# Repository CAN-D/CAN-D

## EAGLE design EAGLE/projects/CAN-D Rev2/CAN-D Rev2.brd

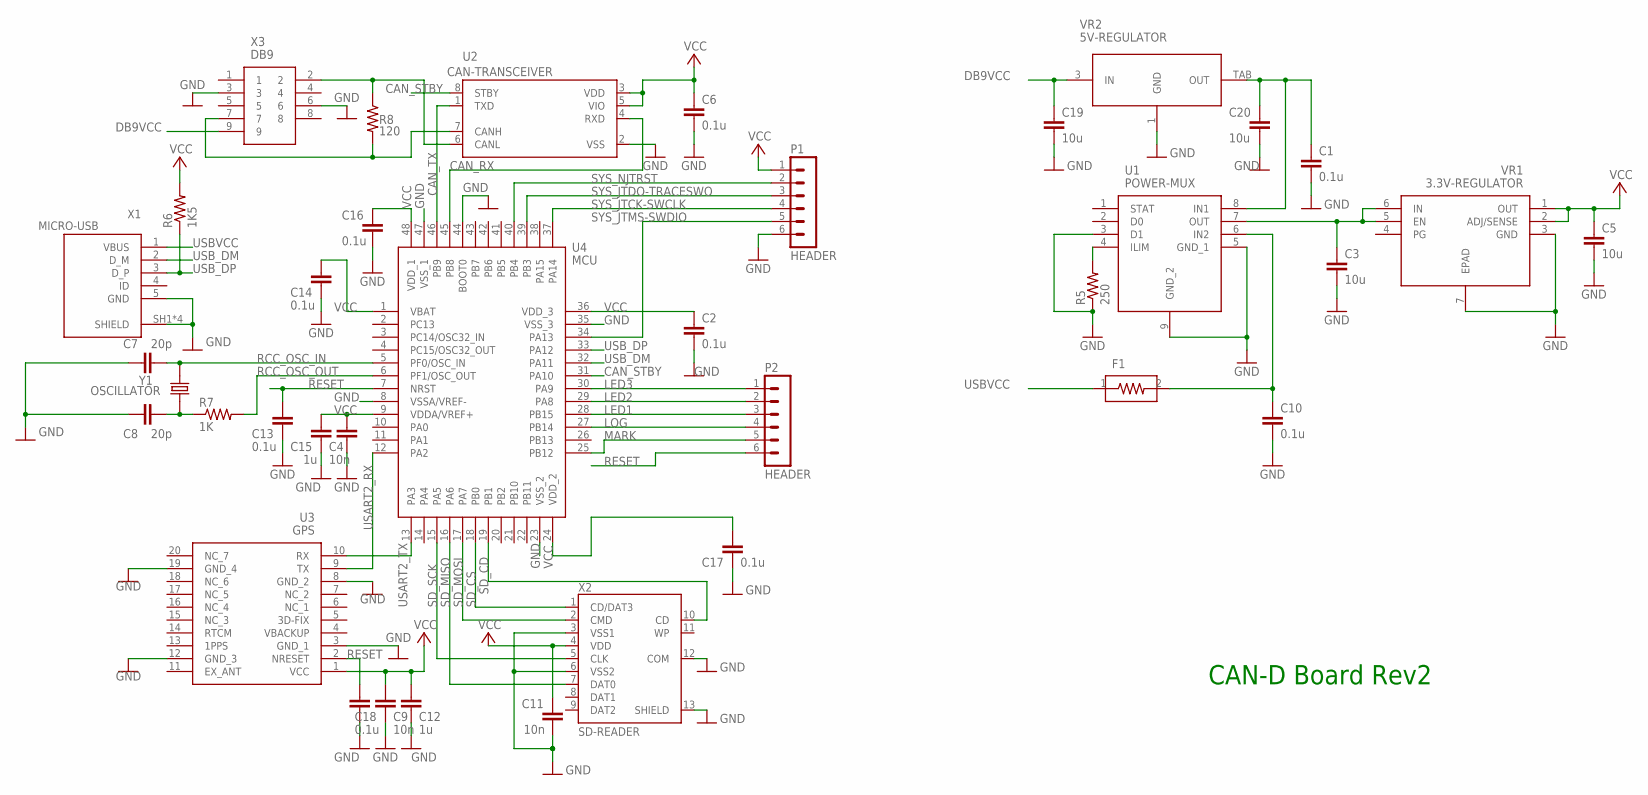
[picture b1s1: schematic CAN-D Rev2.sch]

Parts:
C1, C2, C6, C10, C13, C14, C16, C17, C18: 0.1u; C0603
C3, C5, C19, C20: 10u; C0603
C4, C9, C11: 10n; C0603
C7, C8: 20p; C0603
C12, C15: 1u; C0603
F1: FUSE; 0ZCJ0025FF2E
P1, P2: HEADER; TSM-106-02-L-SV-P-TR
R5: 250; R0603
R6: 1K5; R0603
R7: 1K; R0603
R8: 120; R0603
U1: POWER-MUX; TPS2115ADRBR
U2: CAN-TRANSCEIVER; MCP2562-E/SN
U3: GPS; FGPMMOPA6H
U4: MCU; STM32F302CCT6
VR1: 3.3V-REGULATOR; LD39200PU33R
VR2: 5V-REGULATOR; LD1086D2T50TR
X1: MICRO-USB; DX4R005HJ5R2000
X2: SD-READER; DM1AA-SF-PEJ(21)
X3: DB9; 1-1740195-2
Y1: OSCILLATOR; ABLS-8.000MHZ-B2-T

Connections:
CAN_RX: U2.4 (RXD), U4.45 (PB8)
CAN_STBY: U2.8 (STBY), U4.31 (PA10)
CAN_TX: U2.1 (TXD), U4.46 (PB9)
DB9VCC: C19.1, VR2.3 (IN), X3.9
GND: C1.2, C2.2, C3.2, C4.2, C5.2, C6.2, C7.2, C8.2, C9.2, C10.2, C11.2, C12.2, C13.2, C14.2, C15.2, C16.2, C17.2, C18.2, C19.2, C20.2, P1.6, R5.1, U1.3 (D1), U1.5 (GND_1), U1.9 (GND_2), U2.2 (VSS), U3.3 (GND_1), U3.8 (GND_2), U3.12 (GND_3), U3.19 (GND_4), U4.8 (VSSA/VREF-), U4.23 (VSS_2), U4.35 (VSS_3), U4.44 (BOOT0), U4.47 (VSS_1), VR1.3 (GND), VR1.7 (EPAD), VR2.1 (GND), X1.5 (GND), X1.SH1 (SHIELD), X1.SH2 (SHIELD), X1.SH3 (SHIELD), X1.SH4 (SHIELD), X2.3 (VSS1), X2.6 (VSS2), X2.12 (COM), X2.13 (SHIELD), X3.3, X3.6
LED1: P2.3, U4.28 (PB15)
LED2: P2.2, U4.29 (PA8)
LED3: P2.1, U4.30 (PA9)
LOG: P2.4, U4.27 (PB14)
MARK: P2.5, U4.25 (PB12)
unnamed: C3.1, U1.7 (OUT), VR1.5 (EN), VR1.6 (IN)
unnamed: R8.2, U2.7 (CANH), X3.7
unnamed: C1.1, C20.1, U1.8 (IN1), VR2.TAB (OUT)
unnamed: R8.1, U2.6 (CANL), X3.2
unnamed: R5.2, U1.4 (ILIM)
unnamed: C10.1, F1.2, U1.6 (IN2)
unnamed: C8.1, R7.1, Y1.1
RCC_OSC_IN: C7.1, U4.5 (PF0/OSC_IN), Y1.2
RCC_OSC_OUT: R7.2, U4.6 (PF1/OSC_OUT)
RESET: C13.1, C18.1, P2.6, U3.2 (NRESET), U4.7 (NRST)
SD_CD: U4.19 (PB1), X2.10 (CD)
SD_CS: U4.18 (PB0), X2.1 (CD/DAT3)
SD_MISO: U4.16 (PA6), X2.7 (DAT0)
SD_MOSI: U4.17 (PA7), X2.2 (CMD)
SD_SCK: U4.15 (PA5), X2.5 (CLK)
SYS_JTCK-SWCLK: P1.4, U4.37 (PA14)
SYS_JTDO-TRACESWO: P1.3, U4.39 (PB3)
SYS_JTMS-SWDIO: P1.5, U4.34 (PA13)
SYS_NJTRST: P1.2, U4.40 (PB4)
USART2_RX: U3.9 (TX), U4.12 (PA2)
USART2_TX: U3.10 (RX), U4.13 (PA3)
USBVCC: F1.1, X1.1 (VBUS)
USB_DM: U4.32 (PA11), X1.2 (D_M)
USB_DP: R6.1, U4.33 (PA12), X1.3 (D_P)
VCC: C2.1, C4.1, C5.1, C6.1, C9.1, C11.1, C12.1, C14.1, C15.1, C16.1, C17.1, P1.1, R6.2, U2.3 (VDD), U2.5 (VIO), U3.1 (VCC), U4.1 (VBAT), U4.9 (VDDA/VREF+), U4.24 (VDD_2), U4.36 (VDD_3), U4.48 (VDD_1), VR1.1 (OUT), VR1.2 (ADJ/SENSE), X2.4 (VDD)

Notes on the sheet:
CAN-D Board Rev2

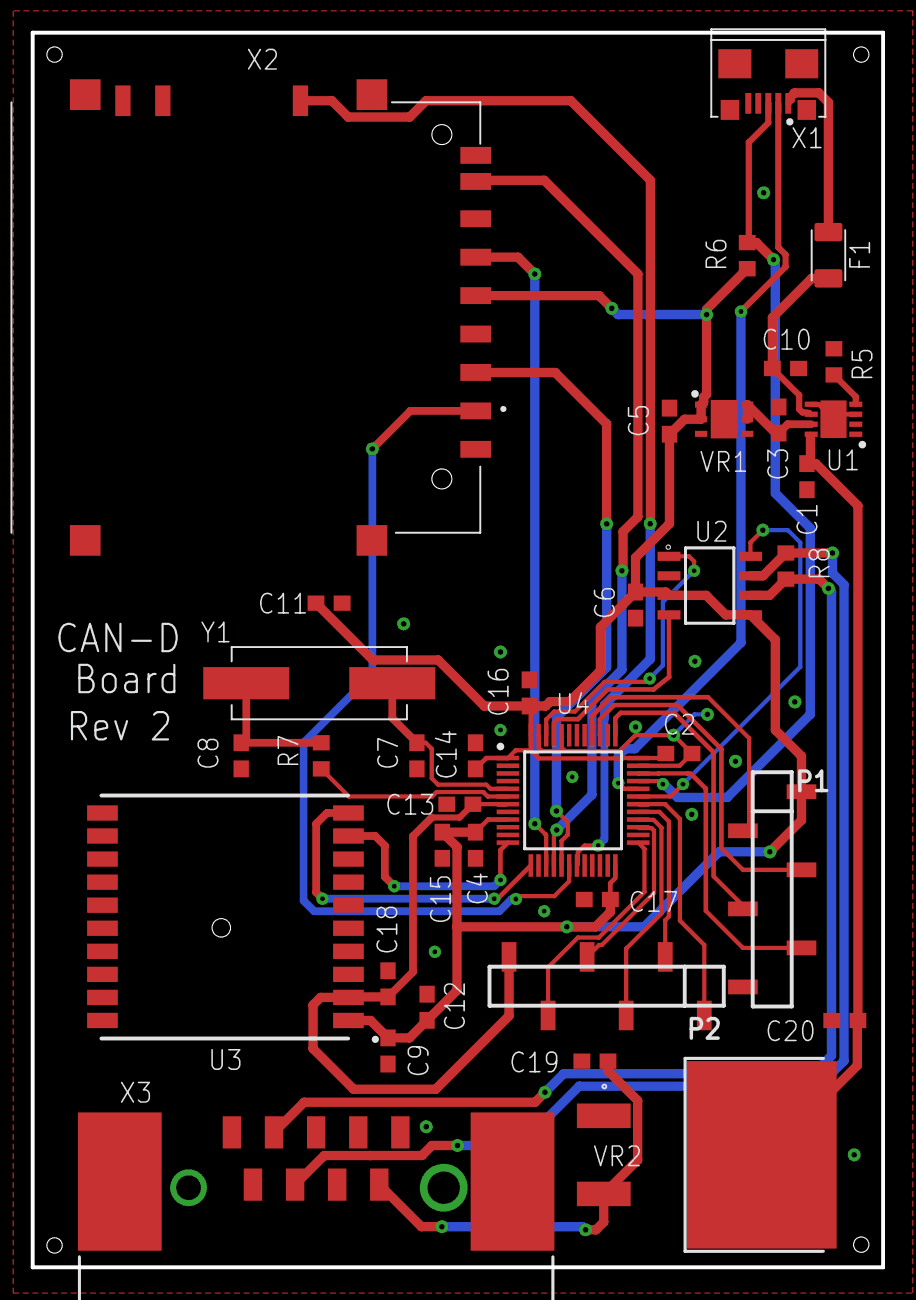
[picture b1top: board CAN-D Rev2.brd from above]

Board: 2 copper layers, 55.3 x 80.3 mm, 37 parts (0 on the bottom side), 35 nets.

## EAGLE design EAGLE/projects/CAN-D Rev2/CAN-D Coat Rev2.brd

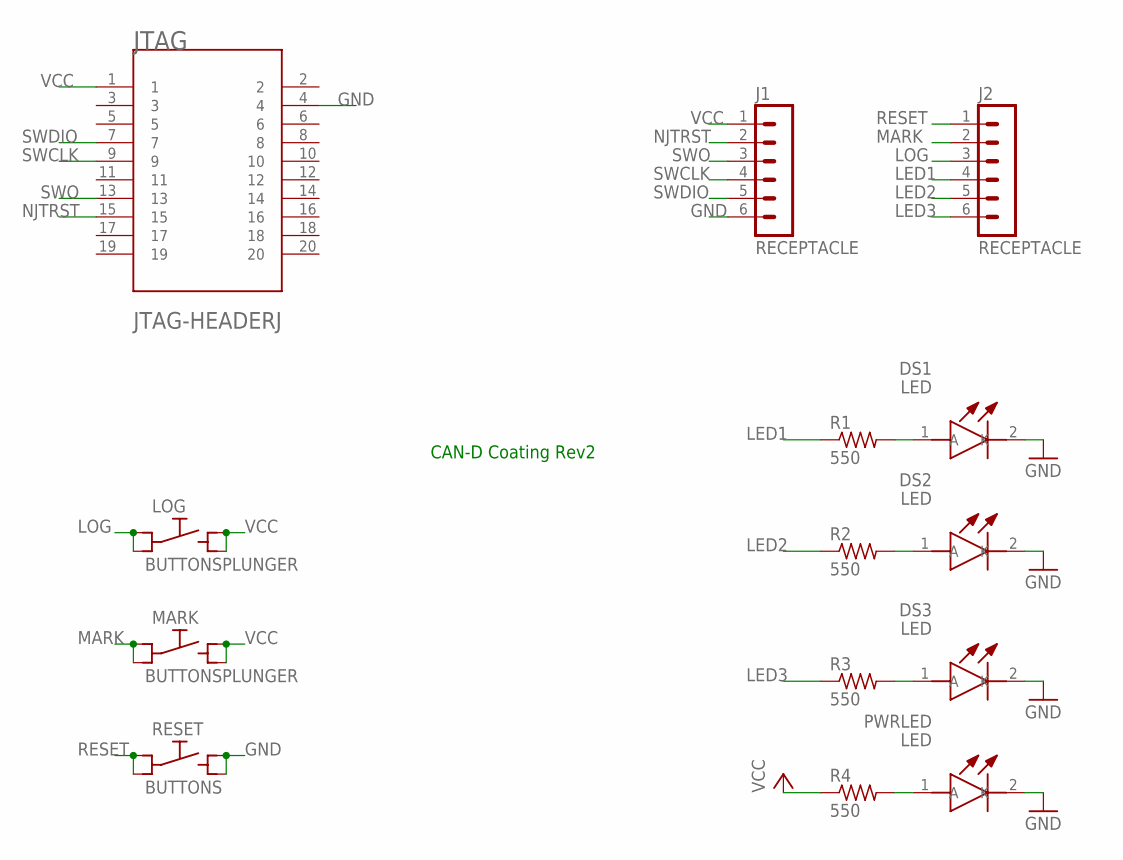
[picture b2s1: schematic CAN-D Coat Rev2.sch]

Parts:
DS1, DS2, DS3: LED; L130-6580001400001
J1, J2: RECEPTACLE; SSM-106-L-SV-K-TR
JTAG: JTAG-HEADERJ; TSM-110-02-S-DV-P-TR
LOG: BUTTONSPLUNGER; TL3301SPF260QG
MARK: BUTTONSPLUNGER; TL3301SPF260QG
PWRLED: LED; L130-6580001400001
R1, R2, R3, R4: 550; R0603
RESET: BUTTONS; 1301.9314

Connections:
GND: DS1.2 (K), DS2.2 (K), DS3.2 (K), J1.6, JTAG.4, PWRLED.2 (K), RESET.NO1 (NO), RESET.NO2 (NO)
LED1: J2.4, R1.1
LED2: J2.5, R2.1
LED3: J2.6, R3.1
LOG: J2.3, LOG.C1 (C), LOG.C2 (C)
MARK: J2.2, MARK.C1 (C), MARK.C2 (C)
unnamed: DS1.1 (A), R1.2
unnamed: DS2.1 (A), R2.2
unnamed: DS3.1 (A), R3.2
unnamed: PWRLED.1 (A), R4.2
NJTRST: J1.2, JTAG.15
RESET: J2.1, RESET.C1 (C), RESET.C2 (C)
SWCLK: J1.4, JTAG.9
SWDIO: J1.5, JTAG.7
SWO: J1.3, JTAG.13
VCC: J1.1, JTAG.1, LOG.NO1 (NO), LOG.NO2 (NO), MARK.NO1 (NO), MARK.NO2 (NO), R4.1

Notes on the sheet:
CAN-D Coating Rev2

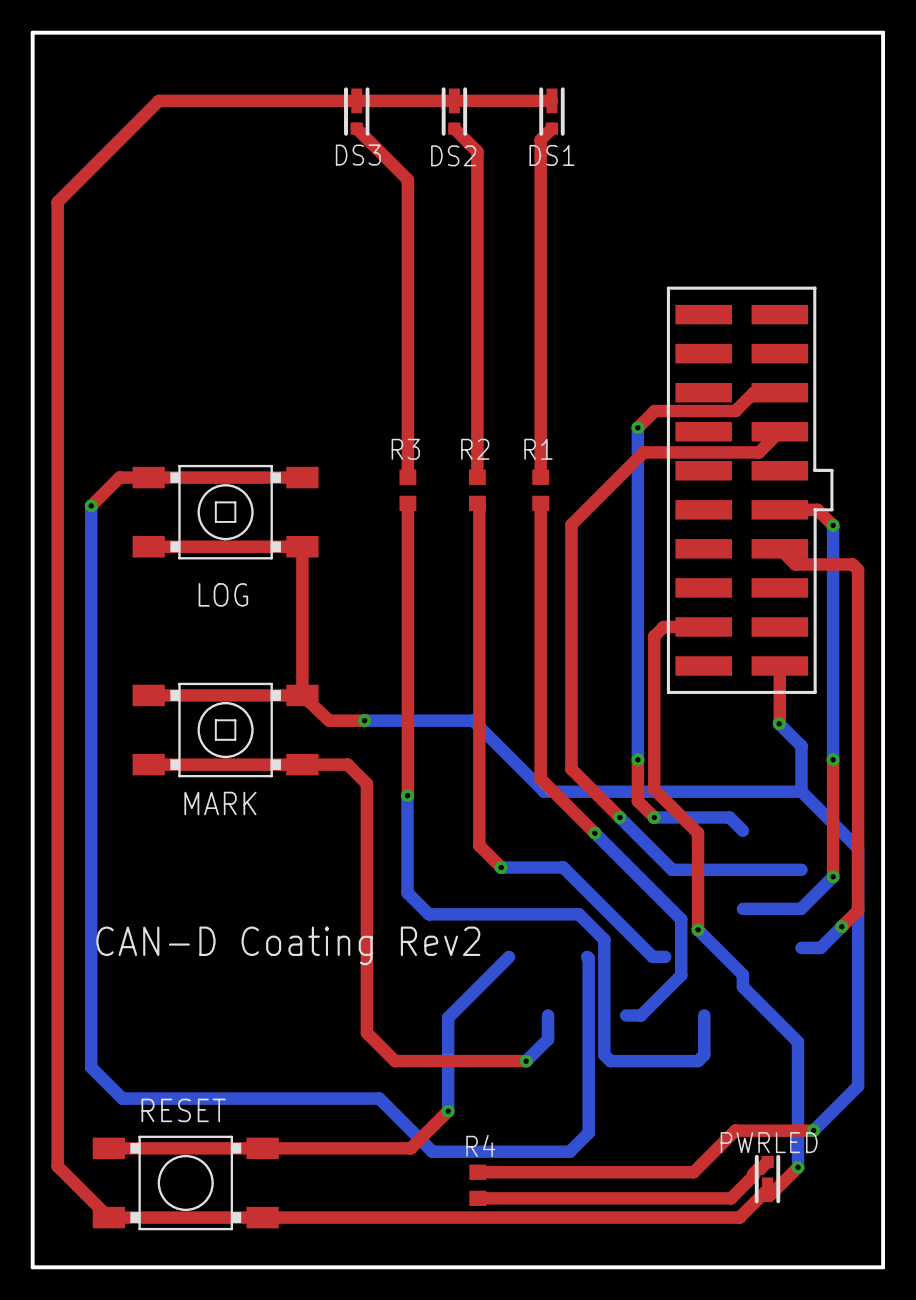
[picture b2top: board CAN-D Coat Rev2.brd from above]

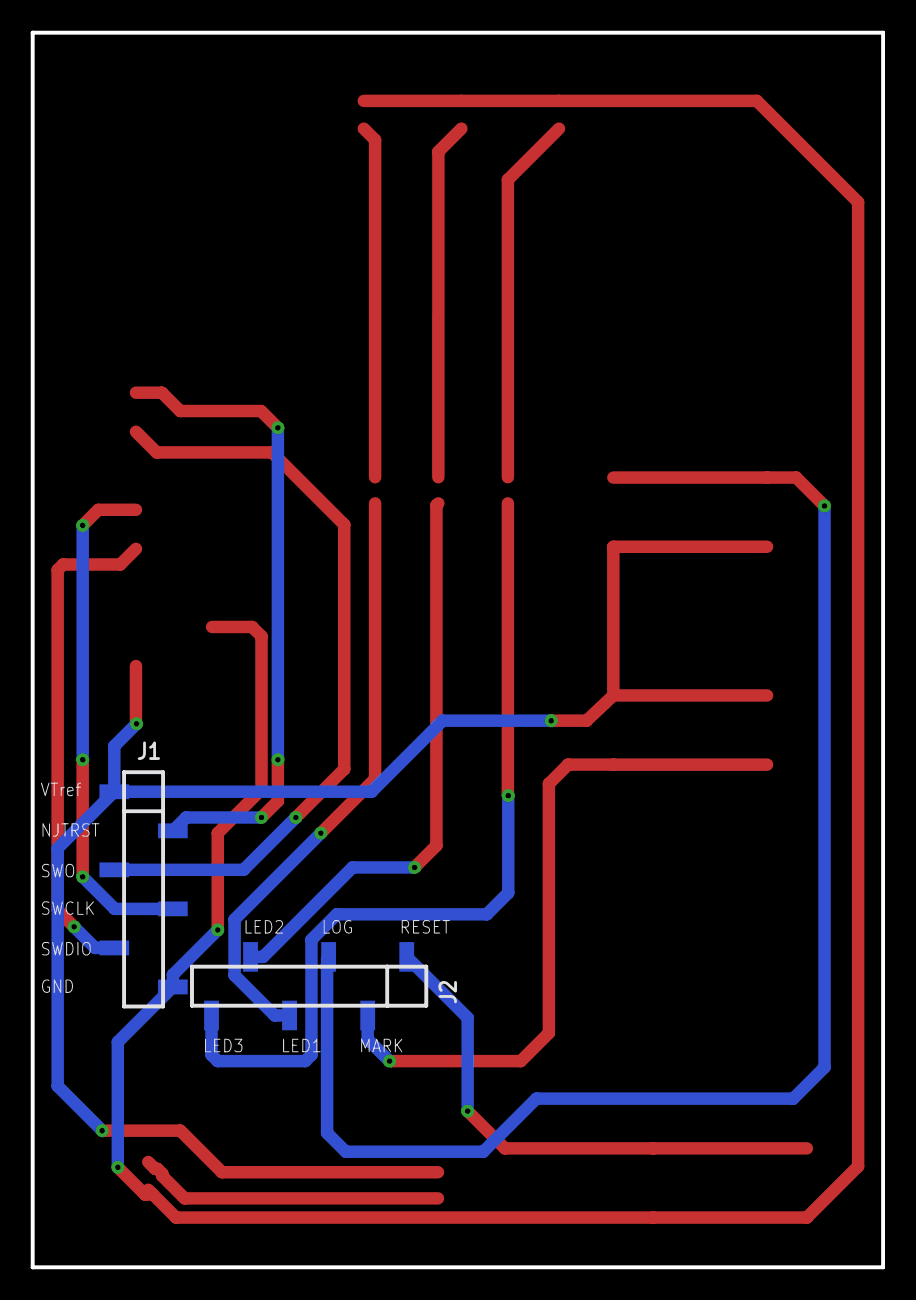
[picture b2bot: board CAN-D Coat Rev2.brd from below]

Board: 2 copper layers, 55.3 x 80.3 mm, 14 parts (2 on the bottom side), 16 nets.

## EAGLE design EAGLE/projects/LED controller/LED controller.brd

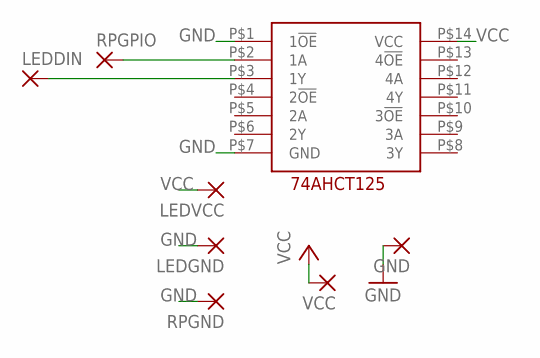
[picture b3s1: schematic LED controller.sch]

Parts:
GND: 1,6/0,9
LEDDIN: 1,6/0,9
LEDGND: 1,6/0,9
LEDVCC: 1,6/0,9
RPGND: 1,6/0,9
RPGPIO: 1,6/0,9
U$1: 74AHCT125N14; N14
VCC: 1,6/0,9

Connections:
GND: GND.1, LEDGND.1, RPGND.1, U$1.P$1 (1!OE!), U$1.P$7 (GND)
unnamed: RPGPIO.1, U$1.P$2 (1A)
unnamed: LEDDIN.1, U$1.P$3 (1Y)
VCC: LEDVCC.1, U$1.P$14 (VCC), VCC.1

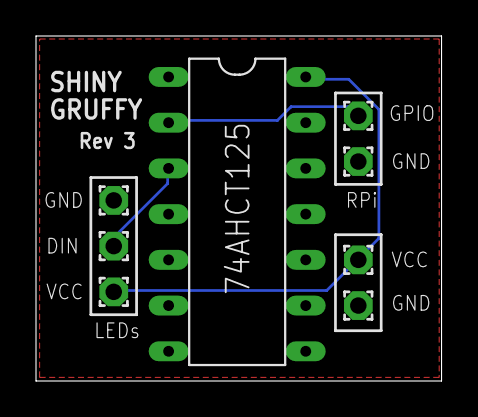
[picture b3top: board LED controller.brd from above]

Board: 2 copper layers, 22.5 x 19.2 mm, 8 parts (0 on the bottom side), 4 nets.

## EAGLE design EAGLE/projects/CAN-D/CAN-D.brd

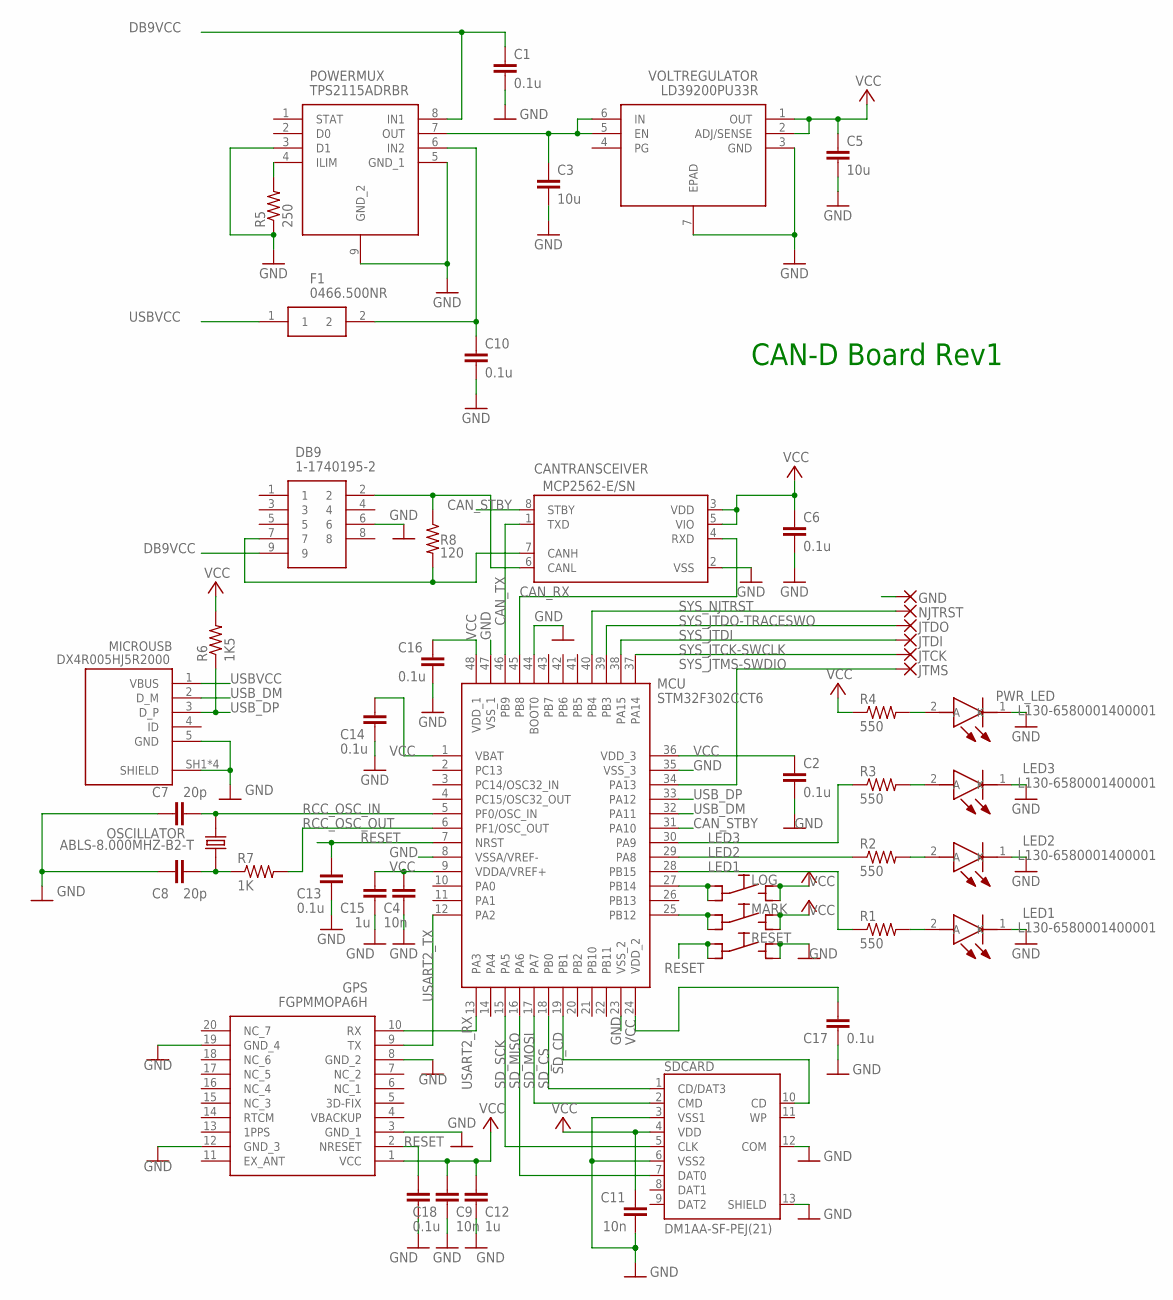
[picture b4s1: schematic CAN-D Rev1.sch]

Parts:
C1, C2, C6, C10, C13, C14, C16, C17, C18: 0.1u; C0603
C3, C5: 10u; C0603
C4, C9, C11: 10n; C0603
C7, C8: 20p; C0603
C12, C15: 1u; C0603
CANTRANSCEIVER: MCP2562-E/SN; SOIC127P600X175-8N
DB9: 1-1740195-2
F1: 0466.500NR; FUSC3215X58N
GND: 2,54/1,1
GPS: FGPMMOPA6H
JTCK: 2,54/1,1
JTDI: 2,54/1,1
JTDO: 2,54/1,1
JTMS: 2,54/1,1
LED1, LED2, LED3: L130-6580001400001
LOG: SCHURTER-LSH-1301.9314; LSH
MARK: SCHURTER-LSH-1301.9314; LSH
MCU: STM32F302CCT6; QFP50P900X900X160-48N
MICROUSB: DX4R005HJ5R2000; JAE_DX4R005HJ5R2000
NJTRST: 2,54/1,1
OSCILLATOR: ABLS-8.000MHZ-B2-T; XTAL_ABLS-8.000MHZ-B2-T
POWERMUX: TPS2115ADRBR; SON65P300X300X100-9N
PWR_LED: L130-6580001400001
R1, R2, R3, R4: 550; R0603
R5: 250; R0603
R6: 1K5; R0603
R7: 1K; R0603
R8: 120; R0603
RESET: SCHURTER-LSH-1301.9314; LSH
SDCARD: DM1AA-SF-PEJ(21); HRS_DM1AA-SF-PEJ(21)
VOLTREGULATOR: LD39200PU33R; SON95P300X300X100-7N

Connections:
CAN_RX: CANTRANSCEIVER.4 (RXD), MCU.45 (PB8)
CAN_STBY: CANTRANSCEIVER.8 (STBY), MCU.31 (PA10)
CAN_TX: CANTRANSCEIVER.1 (TXD), MCU.46 (PB9)
DB9VCC: C1.1, DB9.9, POWERMUX.8 (IN1)
GND: C1.2, C2.2, C3.2, C4.2, C5.2, C6.2, C7.2, C8.2, C9.2, C10.2, C11.2, C12.2, C13.2, C14.2, C15.2, C16.2, C17.2, C18.2, CANTRANSCEIVER.2 (VSS), DB9.6, GND.1, GPS.3 (GND_1), GPS.8 (GND_2), GPS.12 (GND_3), GPS.19 (GND_4), LED1.1 (K), LED2.1 (K), LED3.1 (K), MCU.8 (VSSA/VREF-), MCU.23 (VSS_2), MCU.35 (VSS_3), MCU.44 (BOOT0), MCU.47 (VSS_1), MICROUSB.5 (GND), MICROUSB.SH1 (SHIELD), MICROUSB.SH2 (SHIELD), MICROUSB.SH3 (SHIELD), MICROUSB.SH4 (SHIELD), POWERMUX.3 (D1), POWERMUX.5 (GND_1), POWERMUX.9 (GND_2), PWR_LED.1 (K), R5.1, RESET.NO1 (NO), RESET.NO2 (NO), SDCARD.3 (VSS1), SDCARD.6 (VSS2), SDCARD.12 (COM), SDCARD.13 (SHIELD), VOLTREGULATOR.3 (GND), VOLTREGULATOR.7 (EPAD)
LED1: MCU.28 (PB15), R1.1
LED2: MCU.29 (PA8), R2.1
LED3: MCU.30 (PA9), R3.1
unnamed: C3.1, POWERMUX.7 (OUT), VOLTREGULATOR.5 (EN), VOLTREGULATOR.6 (IN)
unnamed: CANTRANSCEIVER.7 (CANH), DB9.7, R8.2
unnamed: LED1.2 (A), R1.2
unnamed: LED2.2 (A), R2.2
unnamed: LED3.2 (A), R3.2
unnamed: PWR_LED.2 (A), R4.2
unnamed: CANTRANSCEIVER.6 (CANL), DB9.2, R8.1
unnamed: POWERMUX.4 (ILIM), R5.2
unnamed: C10.1, F1.2, POWERMUX.6 (IN2)
unnamed: C8.1, OSCILLATOR.1, R7.1
unnamed: MARK.C1 (C), MARK.C2 (C), MCU.25 (PB12)
unnamed: LOG.C1 (C), LOG.C2 (C), MCU.27 (PB14)
RCC_OSC_IN: C7.1, MCU.5 (PF0/OSC_IN), OSCILLATOR.2
RCC_OSC_OUT: MCU.6 (PF1/OSC_OUT), R7.2
RESET: C13.1, C18.1, GPS.2 (NRESET), MCU.7 (NRST), RESET.C1 (C), RESET.C2 (C)
SD_CD: MCU.19 (PB1), SDCARD.10 (CD)
SD_CS: MCU.18 (PB0), SDCARD.1 (CD/DAT3)
SD_MISO: MCU.16 (PA6), SDCARD.7 (DAT0)
SD_MOSI: MCU.17 (PA7), SDCARD.2 (CMD)
SD_SCK: MCU.15 (PA5), SDCARD.5 (CLK)
SYS_JTCK-SWCLK: JTCK.1, MCU.37 (PA14)
SYS_JTDI: JTDI.1, MCU.38 (PA15)
SYS_JTDO-TRACESWO: JTDO.1, MCU.39 (PB3)
SYS_JTMS-SWDIO: JTMS.1, MCU.34 (PA13)
SYS_NJTRST: MCU.40 (PB4), NJTRST.1
USART2_RX: GPS.10 (RX), MCU.13 (PA3)
USART2_TX: GPS.9 (TX), MCU.12 (PA2)
USBVCC: F1.1, MICROUSB.1 (VBUS)
USB_DM: MCU.32 (PA11), MICROUSB.2 (D_M)
USB_DP: MCU.33 (PA12), MICROUSB.3 (D_P), R6.1
VCC: C2.1, C4.1, C5.1, C6.1, C9.1, C11.1, C12.1, C14.1, C15.1, C16.1, C17.1, CANTRANSCEIVER.3 (VDD), CANTRANSCEIVER.5 (VIO), GPS.1 (VCC), LOG.NO1 (NO), LOG.NO2 (NO), MARK.NO1 (NO), MARK.NO2 (NO), MCU.1 (VBAT), MCU.9 (VDDA/VREF+), MCU.24 (VDD_2), MCU.36 (VDD_3), MCU.48 (VDD_1), R4.1, R6.2, SDCARD.4 (VDD), VOLTREGULATOR.1 (OUT), VOLTREGULATOR.2 (ADJ/SENSE)

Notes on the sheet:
CAN-D Board Rev1

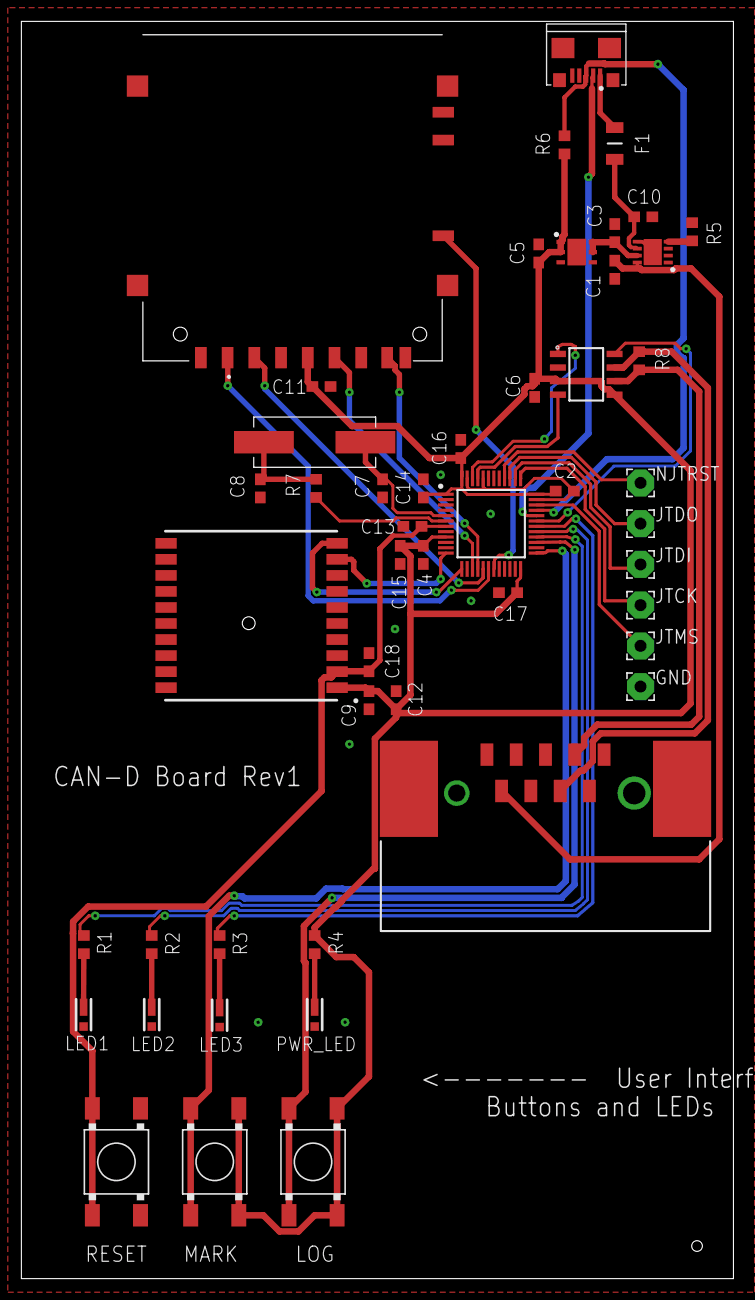
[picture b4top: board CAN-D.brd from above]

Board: 2 copper layers, 66.6 x 117.6 mm, 49 parts (0 on the bottom side), 39 nets.

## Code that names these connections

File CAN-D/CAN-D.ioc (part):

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Mcu.Name=STM32F302C(B-C)Tx
Mcu.Package=LQFP48
Mcu.UserName=STM32F302CCTx
PA11.Mode=Device
PA11.Signal=USB_DM
PA12.Mode=Device
PA12.Signal=USB_DP
PA13.Mode=Serial_Wire
PA13.Signal=SYS_JTMS-SWDIO
PA14.Mode=Serial_Wire
PA14.Signal=SYS_JTCK-SWCLK
PA2.Mode=Asynchronous
PA2.Signal=USART2_TX
PA3.Mode=Asynchronous
PA3.Signal=USART2_RX
PA5.Mode=Full_Duplex_Master
PA5.Signal=SPI1_SCK
PA6.Mode=Full_Duplex_Master
PA6.Signal=SPI1_MISO
PA7.Mode=Full_Duplex_Master
PA7.Signal=SPI1_MOSI
PB8.Mode=Master
PB8.Signal=CAN_RX
PB9.Mode=Master
PB9.Signal=CAN_TX
PF0-OSC_IN.Mode=HSE-External-Oscillator
PF0-OSC_IN.Signal=RCC_OSC_IN
PF1-OSC_OUT.Mode=HSE-External-Oscillator
PF1-OSC_OUT.Signal=RCC_OSC_OUT
RCC.HSEPLLFreq_Value=8000000
RCC.HSE_VALUE=8000000
RCC.SYSCLKFreq_VALUE=48000000
RCC.SYSCLKSourceVirtual=RCC_SYSCLKSOURCE_PLLCLK
board=custom

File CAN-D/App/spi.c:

/**
  ******************************************************************************
  * File Name          : SPI.c
  * Description        : This file provides code for the configuration
  *                      of the SPI instances.
  ******************************************************************************
  */

#include "spi.h"

SPI_HandleTypeDef hspi1;
SPI_HandleTypeDef hspi2;

/* SPI1 init function */
void MX_SPI1_Init(void)
{

  hspi1.Instance = SPI1;
  hspi1.Init.Mode = SPI_MODE_MASTER;
  hspi1.Init.Direction = SPI_DIRECTION_2LINES;
  hspi1.Init.DataSize = SPI_DATASIZE_4BIT;
  hspi1.Init.CLKPolarity = SPI_POLARITY_LOW;
  hspi1.Init.CLKPhase = SPI_PHASE_1EDGE;
  hspi1.Init.NSS = SPI_NSS_SOFT;
  hspi1.Init.BaudRatePrescaler = SPI_BAUDRATEPRESCALER_4;
  hspi1.Init.FirstBit = SPI_FIRSTBIT_MSB;
  hspi1.Init.TIMode = SPI_TIMODE_DISABLE;
  hspi1.Init.CRCCalculation = SPI_CRCCALCULATION_DISABLE;
  hspi1.Init.CRCPolynomial = 7;
  hspi1.Init.CRCLength = SPI_CRC_LENGTH_DATASIZE;
  hspi1.Init.NSSPMode = SPI_NSS_PULSE_ENABLE;
  if (HAL_SPI_Init(&hspi1) != HAL_OK)
  {
    Error_Handler();
  }

}
/* SPI2 init function */
void MX_SPI2_Init(void)
{

  hspi2.Instance = SPI2;
  hspi2.Init.Mode = SPI_MODE_MASTER;
  hspi2.Init.Direction = SPI_DIRECTION_2LINES;
  hspi2.Init.DataSize = SPI_DATASIZE_4BIT;
  hspi2.Init.CLKPolarity = SPI_POLARITY_LOW;
  hspi2.Init.CLKPhase = SPI_PHASE_1EDGE;
  hspi2.Init.NSS = SPI_NSS_SOFT;
  hspi2.Init.BaudRatePrescaler = SPI_BAUDRATEPRESCALER_2;
  hspi2.Init.FirstBit = SPI_FIRSTBIT_MSB;
  hspi2.Init.TIMode = SPI_TIMODE_DISABLE;
  hspi2.Init.CRCCalculation = SPI_CRCCALCULATION_DISABLE;
  hspi2.Init.CRCPolynomial = 7;
  hspi2.Init.CRCLength = SPI_CRC_LENGTH_DATASIZE;
  hspi2.Init.NSSPMode = SPI_NSS_PULSE_ENABLE;
  if (HAL_SPI_Init(&hspi2) != HAL_OK)
  {
    Error_Handler();
  }

}

void HAL_SPI_MspInit(SPI_HandleTypeDef* spiHandle)
{

  GPIO_InitTypeDef GPIO_InitStruct = {0};
  if(spiHandle->Instance==SPI1)
  {
    /* SPI1 clock enable */
    __HAL_RCC_SPI1_CLK_ENABLE();
  
    __HAL_RCC_GPIOA_CLK_ENABLE();
    /**SPI1 GPIO Configuration    
    PA5     ------> SPI1_SCK
    PA6     ------> SPI1_MISO
    PA7     ------> SPI1_MOSI 
    */
    GPIO_InitStruct.Pin = GPIO_PIN_5|GPIO_PIN_6|GPIO_PIN_7;
    GPIO_InitStruct.Mode = GPIO_MODE_AF_PP;
    GPIO_InitStruct.Pull = GPIO_NOPULL;
    GPIO_InitStruct.Speed = GPIO_SPEED_FREQ_HIGH;
    GPIO_InitStruct.Alternate = GPIO_AF5_SPI1;
    HAL_GPIO_Init(GPIOA, &GPIO_InitStruct);

    /* SPI1 interrupt Init */
    HAL_NVIC_SetPriority(SPI1_IRQn, 5, 0);
    HAL_NVIC_EnableIRQ(SPI1_IRQn);
  }
  else if(spiHandle->Instance==SPI2)
  {
    /* SPI2 clock enable */
    __HAL_RCC_SPI2_CLK_ENABLE();
  
    __HAL_RCC_GPIOB_CLK_ENABLE();
    /**SPI2 GPIO Configuration    
    PB13     ------> SPI2_SCK
    PB14     ------> SPI2_MISO
    PB15     ------> SPI2_MOSI 
    */
    GPIO_InitStruct.Pin = GPIO_PIN_13|GPIO_PIN_14|GPIO_PIN_15;
    GPIO_InitStruct.Mode = GPIO_MODE_AF_PP;
    GPIO_InitStruct.Pull = GPIO_NOPULL;
    GPIO_InitStruct.Speed = GPIO_SPEED_FREQ_HIGH;
    GPIO_InitStruct.Alternate = GPIO_AF5_SPI2;
    HAL_GPIO_Init(GPIOB, &GPIO_InitStruct);

    /* SPI2 interrupt Init */
    HAL_NVIC_SetPriority(SPI2_IRQn, 5, 0);
    HAL_NVIC_EnableIRQ(SPI2_IRQn);
  }
}

void HAL_SPI_MspDeInit(SPI_HandleTypeDef* spiHandle)
{

  if(spiHandle->Instance==SPI1)
  {
    /* Peripheral clock disable */
    __HAL_RCC_SPI1_CLK_DISABLE();
  
    /**SPI1 GPIO Configuration    
    PA5     ------> SPI1_SCK
    PA6     ------> SPI1_MISO
    PA7     ------> SPI1_MOSI 
    */
    HAL_GPIO_DeInit(GPIOA, GPIO_PIN_5|GPIO_PIN_6|GPIO_PIN_7);

    /* SPI1 interrupt Deinit */
    HAL_NVIC_DisableIRQ(SPI1_IRQn);
  }
  else if(spiHandle->Instance==SPI2)
  {
    /* Peripheral clock disable */
    __HAL_RCC_SPI2_CLK_DISABLE();
  
    /**SPI2 GPIO Configuration    
    PB13     ------> SPI2_SCK
    PB14     ------> SPI2_MISO
    PB15     ------> SPI2_MOSI 
    */
    HAL_GPIO_DeInit(GPIOB, GPIO_PIN_13|GPIO_PIN_14|GPIO_PIN_15);

    /* SPI2 interrupt Deinit */
    HAL_NVIC_DisableIRQ(SPI2_IRQn);
  }
} 

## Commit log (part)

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2019-01-22 init commit
2019-01-29 Add screenshots of UI
2019-01-31 Add requirements, more screenshots
2019-01-31 Init UI
2019-01-31 Add SPC5 Studio Project
    - The project is located in the CAN-D directory.
    - An application (CAN Data Logger Application)
    has been created.
    - The application is configured to use the
    following low level drivers:
    - PAL, Serial, CAN, SPI, ICU, PWM, IRQ.
2019-02-03 Remove SPC5 Studio Project
    - Removes all files associated with SPC5
    Studio.
    - Adds a README for STM Project Creation.
2019-02-04 Add STM32 CAN-D Project
    - Open the project in STM32CubeMX to
    see the full configuration. (see
    README.md for instructions)
2019-02-04 Adds python specifics to the gitignore
2019-02-04 Adds FW wrapper package
2019-02-04 Readmes are markdowns not makefiles
2019-02-04 Use pyqt5 instead of pyside
2019-02-04 Fix UI directory structure
2019-02-04 variable for readme name
2019-02-05 Remove copyright from app code
    - Removes all copyright headers in app
    files (Src/, Inc/).
    - Also removes code associated with the
    copyright headers (Basically all
    comments that say USER_CODE).
    - Note that I left the usb_device files
2019-02-07 13: Changed src folder to app
2019-02-07 Added FLASH.ld to CAN-D
    - this is needed to build the project.
2019-02-07 Add CAN periph RX interface
    - Adds two callbacks in can.c to handle
    CAN RX data. Each callback handles a
    unique CAN FIFO. Only the callback for
    FIFO0 is implemented for now because
    I am still unsure how these FIFOs
    work.
2019-02-08 Add web files
2019-02-08 add logos, finish trace page
2019-02-08 move icons to a resource file
2019-02-09 Add Makefile and FatFS
    - Adds a Makefile to the CAN-D
    project.
    - Adds the FatFS middleware to
    the CAN-D project.
    - Removes RTC from CAN-D project.
    We don't need this now, so
2019-02-09 Attempt to get the jenkins builder running
2019-02-11 Adds proj dir to Makefile
2019-02-12 Remove comment bloat from usbd_x
2019-02-15 Horizontal expander done, need vertical expander
2019-02-15 Add EAGLE board files + other libraries
2019-02-18 Change UART COM1 name to GPS
2019-02-18 Add UART interface to stm32302c_custom.c driver
2019-02-19 Remove usart.c and cleanup stm32fxx_it.c
    - Removes all dependencies for Src/usart.c.
    - Removes all comment bloat in the interrupts file.
2019-02-20 Fix stm32303c typo
    - Accidentally named some files
    stm32303c instead of stm32302c.
2019-02-20 Fix indentation mismatches
2019-02-20 Remove index tracking from UART IRQ
2019-02-20 Makes all warnings errors.
2019-02-21 Formatting
2019-02-21 Change GPS setting to RMC only
    - GPS is now initialized to only send
    RMC (Recommended Minimum Navigation
    Information) messages, instead of
    RMC and GGA messages.
    - Removes all applicaiton logic associated
    with the GPS GGA data.
2019-02-21 Re-format a few stragglers.
2019-02-21 Rename FatFS exported variables
2019-02-21 Add SD write function
    - Adds APP_FATFS_WriteSD() to fatfs.c
2019-02-21 Adds proto with py and c generated
2019-02-22 Add files for debuggin stm32f3x
2019-02-25 Remove web stuf
2019-03-01 Fix System Clock Config
    - Changes SystemClock_Config() to match the current
    clock tree in the CAN-D.ioc MXCube project.
    - We had changed some peripherals since the project
    code was generated so I generated a clone of our
    current project configuration. I then matched
    our clock config to that of the cloned project.
2019-03-02 Make CAN-D Eclipse project build properly
    - The project can now be built and debugged using eclipse.
2019-03-02 Separate tab contents into a another component
2019-03-02 Change background color
2019-03-03 CAN Tx drivers
2019-03-03 pull new changes
2019-03-04 Moves can stuff out of the bridge.
2019-03-04 Static
2019-03-04 Reworks the CAN rx queue
2019-03-04 Reames bridge to GPS
2019-03-04 Change RTOS Heap Size
    - This fixes the issue where creating more threads
    or queues causes the handles to be NULL.
    - Changes GPS_BUFFER_LENGTH to 2 to use less heap.
    - Removes the LOG BUTTON Task in can.c.
2019-03-04 Fixing the build
2019-03-04 Add GDB host script
2019-03-04 Fix debug scripts
2019-03-04 Check error codes for the threads and queues
2019-03-04 Trouble shooting static mem issues?
2019-03-05 Change expander background
2019-03-05 Fix rxtx test
2019-03-05 rename can-d_gui to gui
2019-03-05 Fix setup.py
2019-03-05 move to a stylesheet folter
2019-03-05 WIP2
2019-03-05 Can demo runs, but nothing happens
2019-03-07 connection tab done, need to fix layouts
2019-03-08 WiP, can might work
2019-03-08 GPS stuff
2019-03-08 Re-Work SPI-SD Interface
2019-03-10 Transmit Table Model done
2019-03-11 Use prebuilt Jenkins image
2019-03-11 Skeletal proto handler
2019-03-13 Receive and Transmit table uses their corresponsing models.
2019-03-14 Add Stop & Start Log Cmd Handlers
    - Adds public functions to can.c to start/stop the
    CAN controller.
2019-03-14 Add Mark Log protobuf cmd handler
2019-03-14 Add RTC to CAN-D project
2019-03-14 Fix eclipse include paths
    - Some include paths weren't global.
2019-03-14 Add SD Card Detection
    - APP_FATFS_WriteSD() now checks if the SD card
    is initialized or not before attempting to
    write data.
    This allows for the user to eject or insert the
    SD card while the app is runnign without breaking
    anything.
2019-03-14 Line changes fix
2019-03-15 Add RTC date/time initialization
2019-03-15 Add unique log filename to can.c
    - The CAN controller will now create a unique
    filename each time it is started.
2019-03-15 Add CAN-D Board Rev2
2019-03-16 Spam the usb with data every second
2019-03-16 Add session counter to fatfs logging
    - FATFS logging now tracks the current session number
    in order to generate unique log identifiers.
    - Peripherals now use APP_FATFS_LogSD() to log data.
    This was to prevent the need for can and gps to
    tracks their own unique log identifiers.
    - When the CAN controller is started, it will now use
2019-03-18 setup backend for connections
2019-03-18 Show message test
2019-03-18 Fix layout of connection.py code
2019-03-18 Populate dropdowns and handle selection changed
2019-03-19 Create models for trace tab
2019-03-19 connect table to model
2019-03-19 Transmit Popup window
2019-03-20 Popup launches from button
2019-03-21 Change MX_ naming ocnvention to APP_
    - Replace the "MX" with "APP" in applicable functions.
2019-03-21 Fix style of edits in transmit window
2019-03-21 disable horizontal scroll bar
2019-03-21 Disable editing of text
2019-03-22 Flesh out USB Transfer App Logic
    - Adds APP_USB_Transmit() to cdc interface. This
    does a check to see if the USB device is connected.
    - Adds a retry limit to USB transfers from the CAN
    and GPS modules.
    - Removes USBStream from the APP_ConfigType. We always
    want to stream usb data so this is useless.
2019-03-22 Remove comments in CAN init/deinit
2019-03-23 Tables scroll to bottom, Re-transmit message button
2019-03-24 Transmit and Receive tables now contain unique values
2019-03-25 Clean up EAGLE files
2019-03-25 Remove magic numbers from SD driver
2019-03-25 Change to nanopb
2019-03-25 Add protobuf-c dependency
2019-03-25 Fix proto build step
2019-03-25 User/bofrim/nanopb (#106)
    * Change to nanopb
    * Fix proto build step
    * Single step build
2019-03-25 Static array sizes in proto
2019-03-26 Static array sizes in proto (#108)
2019-03-26 Add Forced Enumeration to USB CDC
2019-03-26 WIP creating the connector
2019-03-26 Polling
2019-03-26 Better return type and swap order in switch statement
2019-03-26 Fix the func name so it works with entry p
2019-03-26 Uses blocking queues for can recv
2019-03-26 Sends commands to device
2019-03-26 Adds command scripts
2019-03-26 Add cantools and sample dbc
2019-03-26 Change protobuf-c to protobuf
2019-03-27 Add ui for filtering trace table
2019-03-29 Test decoding incoming messages
2019-03-29 Fix RTOS heap size
    - Changes the RTOS heap size back to 1024*5
    - Changes the stack size for the CANMonitorTask
    back to 256.
2019-03-29 Change serialization for new protobuf config
    - Also changes the gpsDataChunk size to 128 bytes.
2019-03-29 Add Protobuf packing to GPS module
2019-03-29 Add candy_connector to requirements
2019-03-29 Connect buttons to function
2019-03-29 remove msg type
2019-03-30 Reworking can protobuf msg struct
2019-03-30 Simple test for CAN & GPS USB transmit
2019-03-30 Test with canned data
2019-03-30 Uses threads to append incoming data from the connector to the tables
2019-03-30 Fix transmitting bug
2019-03-30 Fill out the mock interface
2019-03-30 Hook SD log and stop log buttons
2019-03-30 Add filepicker to trace window
2019-03-31 Updates the scripts so they're actually async.
2019-03-31 Remove magic numbers from CAN & GPS modules
2019-03-31 Test treeview
2019-03-31 Change treeview to tableview for the production branch
2019-03-31 Add SD data formatting to CAN
    - Also changes the CAN and GPS LOG_FILENAME
    defines to LOG_IDENTIFIER
2019-03-31 Add IRQ Handler for SD Detect
2019-03-31 Add linecounter to FatFS module
2019-03-31 Remove all logs in APP_FATFS_Init()
2019-04-01 Remove connection and gps tab
2019-04-01 Remove test data in can.c
2019-04-01 Fix LED for active high
    - was configured as active low
2019-04-01 Remove Reset Button from BSP
    - The Reset Button is not tied to any GPIO so it
    does not need to be in BSP
2019-04-03 Statusbar works
2019-04-04 Can open and save can-d trace files
2019-04-04 Update icons to newer and bigger designs made by Brett
2019-04-05 Resize icon
2019-04-05 More styling
2019-04-05 Generate data from is350 dbc
2019-04-05 Add trace files
2019-04-05 Mark button works
2019-04-07 Asynchronously transmits messages
2019-04-08 Added transmitData to proto
2019-04-08 CAN TX Demo Code
    - Use the CAN_TX_ON define to enabled/disable
    CAN Tx.
    - CAN is in LOOPBACK Mode by default now (in CAN_Init()).
2019-04-08 Clean up mark-log stuff
2019-04-08 Adds loopback test script
2019-04-08 Stop usb after lb test
2019-04-08 fixes a missing message
2019-04-09 Add to count everytime message is transmitted
2019-04-09 Finish documentation
2019-04-09 Fix Transmit Bug in Gooey
    - The tx msg ID was a str and needed to be an int.
    - The tx msg data was a str and needed to be a list.
2019-04-09 Adds a new cmd to avoid one not working
2019-04-09 Update pb file
2019-04-09 Add dlc field to proto
2019-04-09 Use dlc when passing can msg
2019-04-09 Appends 0
2019-04-09 Validates length and data field
2019-04-09 Actually sets the DLC field for the to embd msg
2019-04-09 Make CAN rx/tx use header dlc info
2019-04-09 Check DLC FromeEmbedded field
2019-04-09 Add loopback mode, fix cycle time for received messages
2019-04-09 Cleanup interrupts file
    - Added a blurb about infinite while loop handlers.
2019-04-09 Add briefs to all CAN functions
2019-04-09 Add briefs to fatfs file
2019-04-09 Add briefs to rtc file
2019-04-09 Cleanup Inc/
2019-04-09 Add briefs to proto_handler file
2019-04-09 Add signals to previously updated messages
2019-04-10 Change to teal
2019-04-10 Cleanup FATFS_LogSD()
2019-04-10 Fix MarkLog Task Hardfault
    - Had to increase the task size to 256
2019-04-11 Dont reinstantiate the CANDBUS on connect
2019-04-11 Fix mark log bug
2019-04-11 Final Demo Define
2019-04-11 kill all tasks on disconnect
2019-04-11 Demo data
2019-04-12 Revert "Final Demo Define"
    This reverts commit b42a0e109ad8e7247dd9af530c61bfe7f1ffa71c.
